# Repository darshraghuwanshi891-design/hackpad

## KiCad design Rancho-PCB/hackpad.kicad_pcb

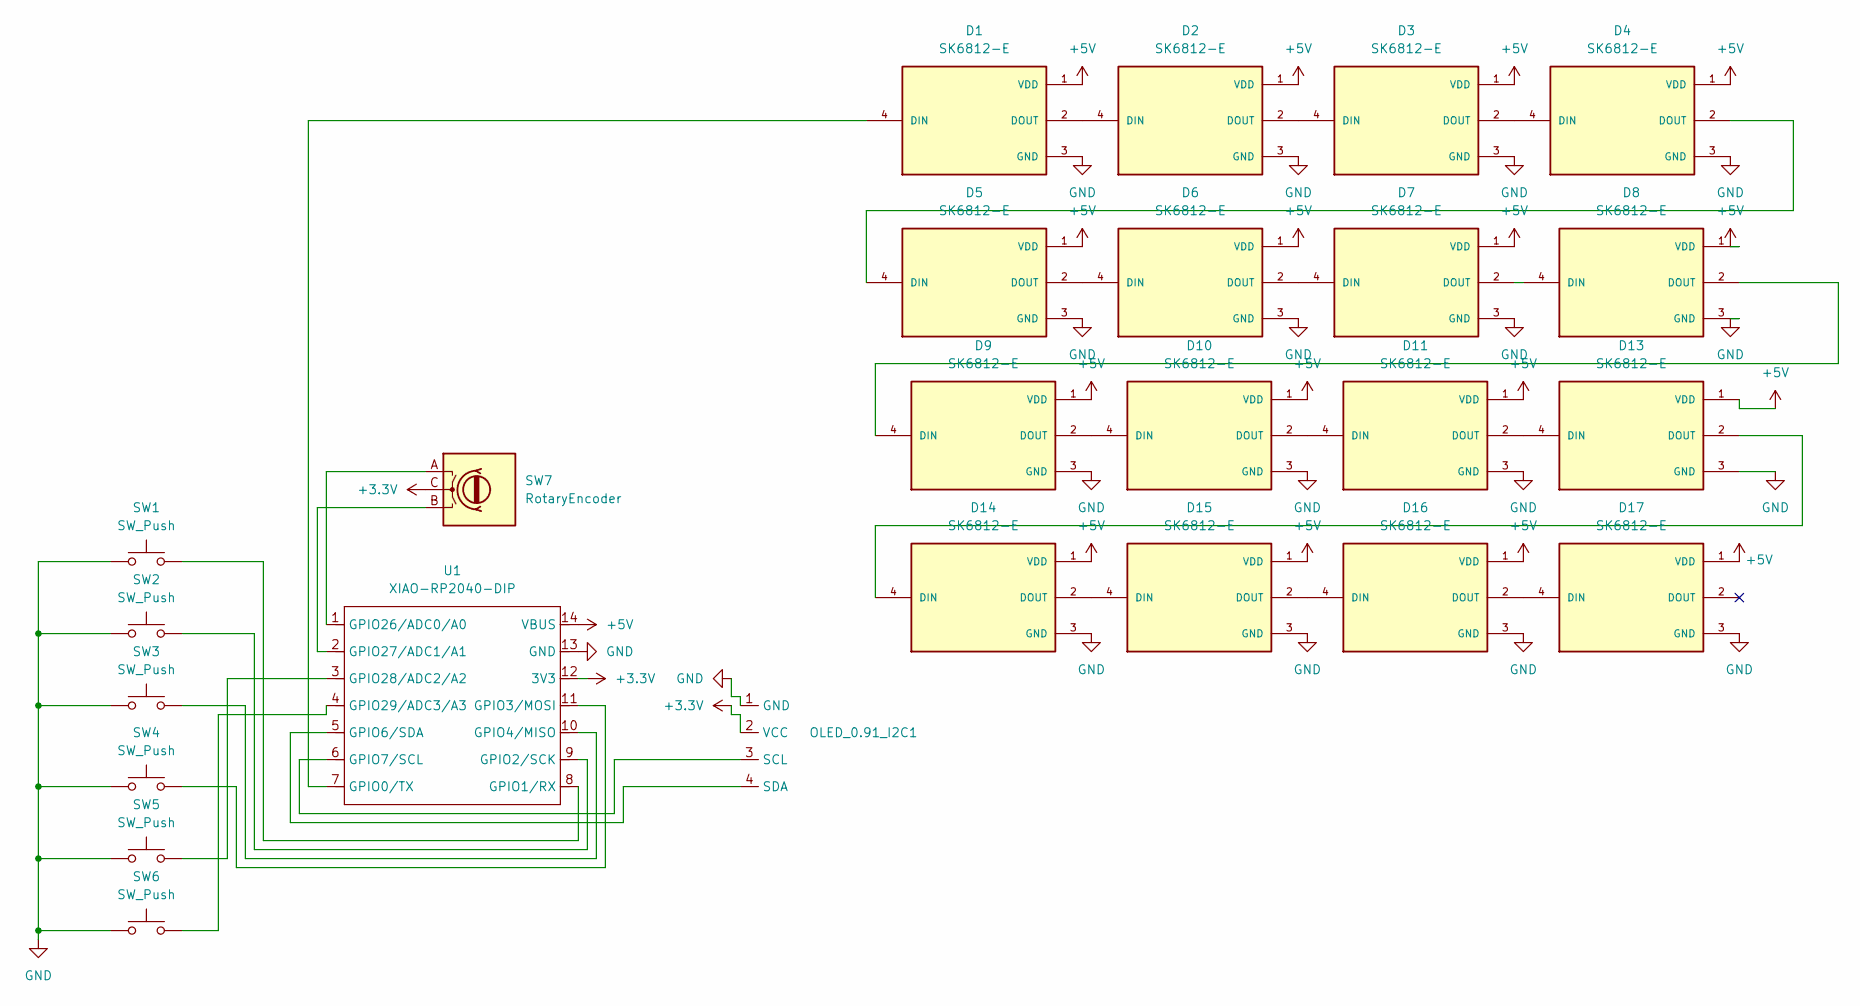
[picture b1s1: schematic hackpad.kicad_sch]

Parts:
D1, D2, D3, D4, D5, D6, D7, D8, D9, D10, D11, D13, D14, D15, D16, D17: SK6812-E; LED_SK6812-E; PARTREV 2
OLED_0.91_I2C1: SSD1306-0.91-OLED-4pin-128x32
SW1, SW2, SW3, SW4, SW5, SW6: SW_Push; SW_Cherry_MX_1.00u_PCB
SW7: RotaryEncoder; RotaryEncoder_Alps_EC11E_Vertical_H20mm
U1: XIAO-RP2040-DIP

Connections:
+3.3V: OLED_0.91_I2C1.2 (VCC), SW7.C, U1.12 (3V3)
+5V: D1.1 (VDD), D2.1 (VDD), D3.1 (VDD), D4.1 (VDD), D5.1 (VDD), D6.1 (VDD), D7.1 (VDD), D8.1 (VDD), D9.1 (VDD), D10.1 (VDD), D11.1 (VDD), D13.1 (VDD), D14.1 (VDD), D15.1 (VDD), D16.1 (VDD), D17.1 (VDD), U1.14 (VBUS)
GND: D1.3 (GND), D2.3 (GND), D3.3 (GND), D4.3 (GND), D5.3 (GND), D6.3 (GND), D7.3 (GND), D8.3 (GND), D9.3 (GND), D10.3 (GND), D11.3 (GND), D13.3 (GND), D14.3 (GND), D15.3 (GND), D16.3 (GND), D17.3 (GND), OLED_0.91_I2C1.1 (GND), SW1.1, SW2.1, SW3.1, SW4.1, SW5.1, SW6.1, U1.13 (GND)
unnamed: D1.4 (DIN), U1.7 (GPIO0/TX)
unnamed: D1.2 (DOUT), D2.4 (DIN)
unnamed: D2.2 (DOUT), D3.4 (DIN)
unnamed: D3.2 (DOUT), D4.4 (DIN)
unnamed: D4.2 (DOUT), D5.4 (DIN)
unnamed: D5.2 (DOUT), D6.4 (DIN)
unnamed: D6.2 (DOUT), D7.4 (DIN)
unnamed: D7.2 (DOUT), D8.4 (DIN)
unnamed: D8.2 (DOUT), D9.4 (DIN)
unnamed: D9.2 (DOUT), D10.4 (DIN)
unnamed: D10.2 (DOUT), D11.4 (DIN)
unnamed: D11.2 (DOUT), D13.4 (DIN)
unnamed: D13.2 (DOUT), D14.4 (DIN)
unnamed: D14.2 (DOUT), D15.4 (DIN)
unnamed: D15.2 (DOUT), D16.4 (DIN)
unnamed: D16.2 (DOUT), D17.4 (DIN)
unnamed: OLED_0.91_I2C1.3 (SCL), U1.6 (GPIO7/SCL)
unnamed: OLED_0.91_I2C1.4 (SDA), U1.5 (GPIO6/SDA)
unnamed: SW1.2, U1.8 (GPIO1/RX)
unnamed: SW2.2, U1.9 (GPIO2/SCK)
unnamed: SW4.2, U1.11 (GPIO3/MOSI)
unnamed: SW3.2, U1.10 (GPIO4/MISO)
unnamed: SW7.A, U1.1 (GPIO26/ADC0/A0)
unnamed: SW7.B, U1.2 (GPIO27/ADC1/A1)
unnamed: SW5.2, U1.3 (GPIO28/ADC2/A2)
unnamed: SW6.2, U1.4 (GPIO29/ADC3/A3)

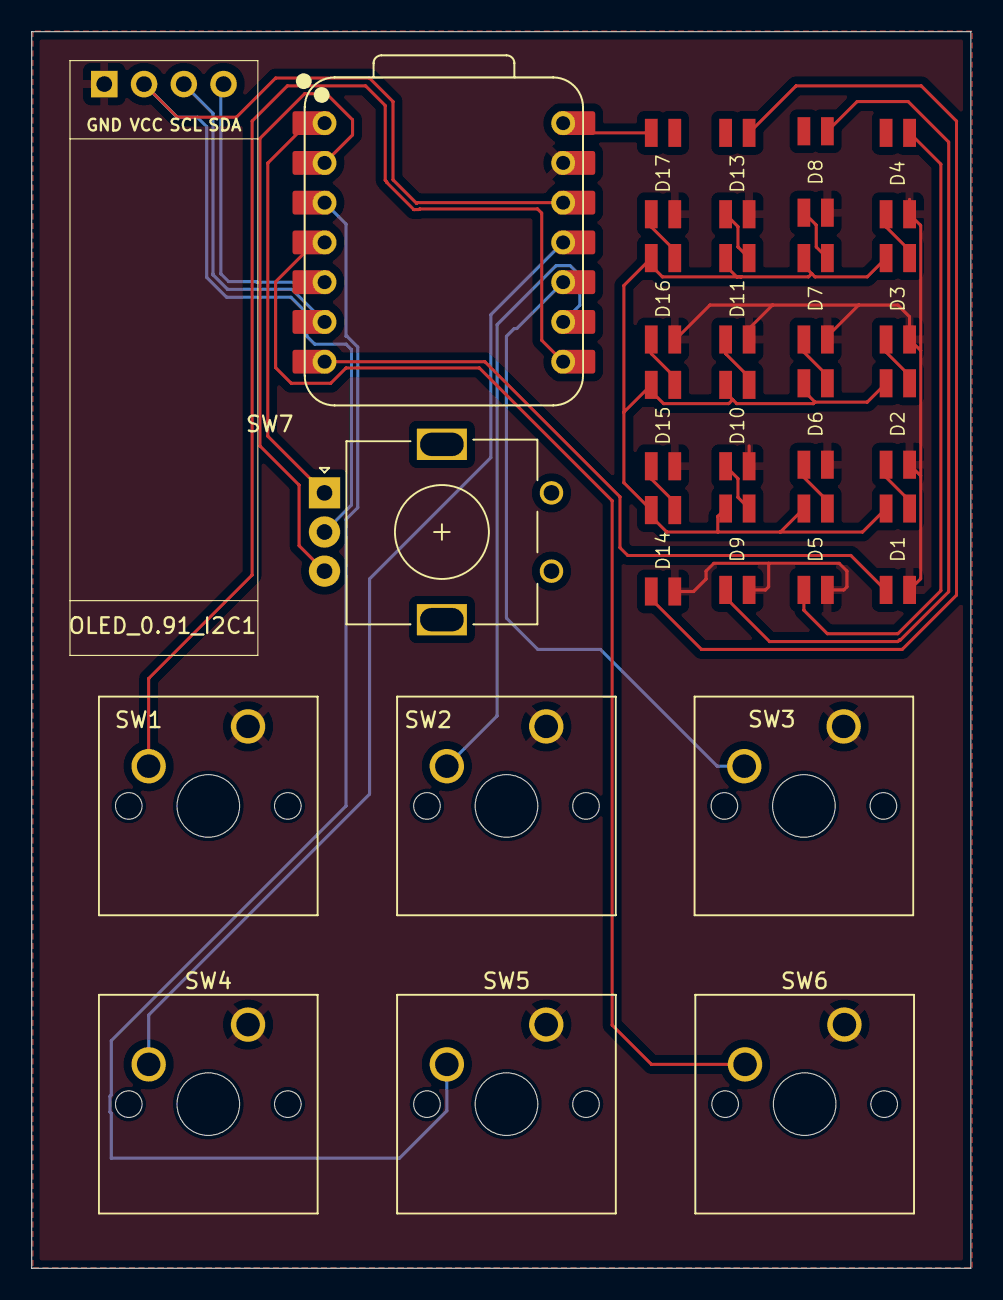
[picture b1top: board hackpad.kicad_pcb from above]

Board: 2 copper layers, 60.0 x 79.0 mm, 25 parts (0 on the bottom side), 29 nets.
